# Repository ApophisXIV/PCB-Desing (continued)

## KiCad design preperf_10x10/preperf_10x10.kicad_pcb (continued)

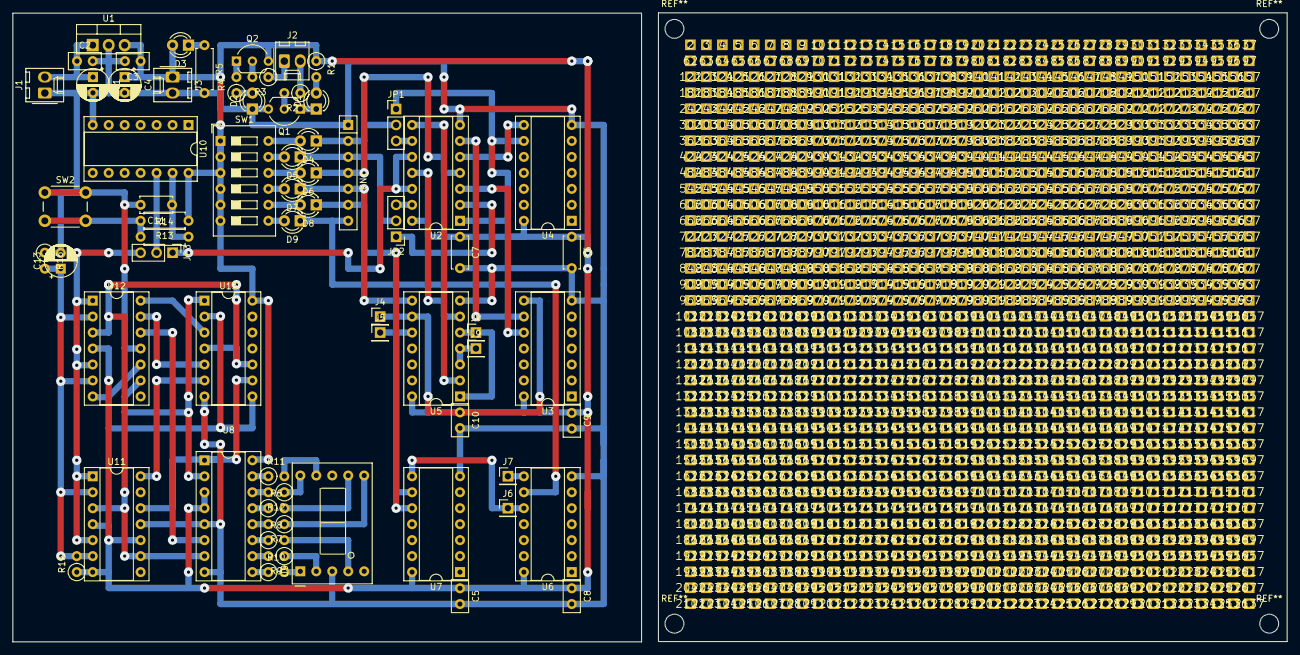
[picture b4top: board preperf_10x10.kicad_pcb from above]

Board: 2 copper layers, 202.7 x 100.1 mm, 1363 parts (0 on the bottom side), 67 nets.

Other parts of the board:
2, 3, 4, 5, 6, 7, 8, 9, 10, 11, 12, 13, 14, 15, 16, 17, 18, 19, 20, 21, 22, 23, 24, 25, 26, 27, 28, 29, 30, 31, 32, 33, 34, 35, 36, 37, 62, 63, 64, 65, 66, 67, 68, 69, 70, 71, 72, 73, 74, 75, 76, 77, 78, 79, 80, 81, 82, 83, 84, 85, 86, 87, 88, 89, 90, 91, 92, 93, 94, 95, 96, 97, 122, 123, 124, 125, 126, 127, 128, 129, 130, 131, 132, 133, 134, 135, 136, 137, 138, 139, 140, 141, 142, 143, 144, 145, 146, 147, 148, 149, 150, 151, 152, 153, 154, 155, 156, 157, 182, 183, 184, 185, 186, 187, 188, 189, 190, 191, 192, 193, 194, 195, 196, 197, 198, 199, 200, 201, 202, 203, 204, 205, 206, 207, 208, 209, 210, 211, 212, 213, 214, 215, 216, 217, 242, 243, 244, 245, 246, 247, 248, 249, 250, 251, 252, 253, 254, 255, 256, 257, 258, 259, 260, 261, 262, 263, 264, 265, 266, 267, 268, 269, 270, 271, 272, 273, 274, 275, 276, 277, 302, 303, 304, 305, 306, 307, 308, 309, 310, 311, 312, 313, 314, 315, 316, 317, 318, 319, 320, 321, 322, 323, 324, 325, 326, 327, 328, 329, 330, 331, 332, 333, 334, 335, 336, 337, 362, 363, 364, 365, 366, 367, 368, 369, 370, 371, 372, 373, 374, 375, 376, 377, 378, 379, 380, 381, 382, 383, 384, 385, 386, 387, 388, 389, 390, 391, 392, 393, 394, 395, 396, 397, 422, 423, 424, 425, 426, 427, 428, 429, 430, 431, 432, 433, 434, 435, 436, 437, 438, 439, 440, 441, 442, 443, 444, 445, 446, 447, 448, 449, 450, 451, 452, 453, 454, 455, 456, 457, 482, 483, 484, 485, 486, 487, 488, 489, 490, 491, 492, 493, 494, 495, 496, 497, 498, 499, 500, 501, 502, 503, 504, 505, 506, 507, 508, 509, 510, 511, 512, 513, 514, 515, 516, 517, 542, 543, 544, 545, 546, 547, 548, 549, 550, 551, 552, 553, 554, 555, 556, 557, 558, 559, 560, 561, 562, 563, 564, 565, 566, 567, 568, 569, 570, 571, 572, 573, 574, 575, 576, 577, 602, 603, 604, 605, 606, 607, 608, 609, 610, 611, 612, 613, 614, 615, 616, 617, 618, 619, 620, 621, 622, 623, 624, 625, 626, 627, 628, 629, 630, 631, 632, 633, 634, 635, 636, 637, 662, 663, 664, 665, 666, 667, 668, 669, 670, 671, 672, 673, 674, 675, 676, 677, 678, 679, 680, 681, 682, 683, 684, 685, 686, 687, 688, 689, 690, 691, 692, 693, 694, 695, 696, 697, 722, 723, 724, 725, 726, 727, 728, 729, 730, 731, 732, 733, 734, 735, 736, 737, 738, 739, 740, 741, 742, 743, 744, 745, 746, 747, 748, 749, 750, 751, 752, 753, 754, 755, 756, 757, 782, 783, 784, 785, 786, 787, 788, 789, 790, 791, 792, 793, 794, 795, 796, 797, 798, 799, 800, 801, 802, 803, 804, 805, 806, 807, 808, 809, 810, 811, 812, 813, 814, 815, 816, 817, 842, 843, 844, 845, 846, 847, 848, 849, 850, 851, 852, 853, 854, 855, 856, 857, 858, 859, 860, 861, 862, 863, 864, 865, 866, 867, 868, 869, 870, 871, 872, 873, 874, 875, 876, 877, 902, 903, 904, 905, 906, 907, 908, 909, 910, 911, 912, 913, 914, 915, 916, 917, 918, 919, 920, 921, 922, 923, 924, 925, 926, 927, 928, 929, 930, 931, 932, 933, 934, 935, 936, 937, 962, 963, 964, 965, 966, 967, 968, 969, 970, 971, 972, 973, 974, 975, 976, 977, 978, 979, 980, 981, 982, 983, 984, 985, 986, 987, 988, 989, 990, 991, 992, 993, 994, 995, 996, 997, 1022, 1023, 1024, 1025, 1026, 1027, 1028, 1029, 1030, 1031, 1032, 1033, 1034, 1035, 1036, 1037, 1038, 1039, 1040, 1041, 1042, 1043, 1044, 1045, 1046, 1047, 1048, 1049, 1050, 1051, 1052, 1053, 1054, 1055, 1056, 1057, 1082, 1083, 1084, 1085, 1086, 1087, 1088, 1089, 1090, 1091, 1092, 1093, 1094, 1095, 1096, 1097, 1098, 1099, 1100, 1101, 1102, 1103, 1104, 1105, 1106, 1107, 1108, 1109, 1110, 1111, 1112, 1113, 1114, 1115, 1116, 1117, 1142, 1143, 1144, 1145, 1146, 1147, 1148, 1149, 1150, 1151, 1152, 1153, 1154, 1155, 1156, 1157, 1158, 1159, 1160, 1161, 1162, 1163, 1164, 1165, 1166, 1167, 1168, 1169, 1170, 1171, 1172, 1173, 1174, 1175, 1176, 1177, 1202, 1203, 1204, 1205, 1206, 1207, 1208, 1209, 1210, 1211, 1212, 1213, 1214, 1215, 1216, 1217, 1218, 1219, 1220, 1221, 1222, 1223, 1224, 1225, 1226, 1227, 1228, 1229, 1230, 1231, 1232, 1233, 1234, 1235, 1236, 1237, 1262, 1263, 1264, 1265, 1266, 1267, 1268, 1269, 1270, 1271, 1272, 1273, 1274, 1275, 1276, 1277, 1278, 1279, 1280, 1281, 1282, 1283, 1284, 1285, 1286, 1287, 1288, 1289, 1290, 1291, 1292, 1293, 1294, 1295, 1296, 1297, 1322, 1323, 1324, 1325, 1326, 1327, 1328, 1329, 1330, 1331, 1332, 1333, 1334, 1335, 1336, 1337, 1338, 1339, 1340, 1341, 1342, 1343, 1344, 1345, 1346, 1347, 1348, 1349, 1350, 1351, 1352, 1353, 1354, 1355, 1356, 1357, 1382, 1383, 1384, 1385, 1386, 1387, 1388, 1389, 1390, 1391, 1392, 1393, 1394, 1395, 1396, 1397, 1398, 1399, 1400, 1401, 1402, 1403, 1404, 1405, 1406, 1407, 1408, 1409, 1410, 1411, 1412, 1413, 1414, 1415, 1416, 1417, 1442, 1443, 1444, 1445, 1446, 1447, 1448, 1449, 1450, 1451, 1452, 1453, 1454, 1455, 1456, 1457, 1458, 1459, 1460, 1461, 1462, 1463, 1464, 1465, 1466, 1467, 1468, 1469, 1470, 1471, 1472, 1473, 1474, 1475, 1476, 1477, 1502, 1503, 1504, 1505, 1506, 1507, 1508, 1509, 1510, 1511, 1512, 1513, 1514, 1515, 1516, 1517, 1518, 1519, 1520, 1521, 1522, 1523, 1524, 1525, 1526, 1527, 1528, 1529, 1530, 1531, 1532, 1533, 1534, 1535, 1536, 1537, 1562, 1563, 1564, 1565, 1566, 1567, 1568, 1569, 1570, 1571, 1572, 1573, 1574, 1575, 1576, 1577, 1578, 1579, 1580, 1581, 1582, 1583, 1584, 1585, 1586, 1587, 1588, 1589, 1590, 1591, 1592, 1593, 1594, 1595, 1596, 1597, 1622, 1623, 1624, 1625, 1626, 1627, 1628, 1629, 1630, 1631, 1632, 1633, 1634, 1635, 1636, 1637, 1638, 1639, 1640, 1641, 1642, 1643, 1644, 1645, 1646, 1647, 1648, 1649, 1650, 1651, 1652, 1653, 1654, 1655, 1656, 1657, 1682, 1683, 1684, 1685, 1686, 1687, 1688, 1689, 1690, 1691, 1692, 1693, 1694, 1695, 1696, 1697, 1698, 1699, 1700, 1701, 1702, 1703, 1704, 1705, 1706, 1707, 1708, 1709, 1710, 1711, 1712, 1713, 1714, 1715, 1716, 1717, 1742, 1743, 1744, 1745, 1746, 1747, 1748, 1749, 1750, 1751, 1752, 1753, 1754, 1755, 1756, 1757, 1758, 1759, 1760, 1761, 1762, 1763, 1764, 1765, 1766, 1767, 1768, 1769, 1770, 1771, 1772, 1773, 1774, 1775, 1776, 1777, 1802, 1803, 1804, 1805, 1806, 1807, 1808, 1809, 1810, 1811, 1812, 1813, 1814, 1815, 1816, 1817, 1818, 1819, 1820, 1821, 1822, 1823, 1824, 1825, 1826, 1827, 1828, 1829, 1830, 1831, 1832, 1833, 1834, 1835, 1836, 1837, 1862, 1863, 1864, 1865, 1866, 1867, 1868, 1869, 1870, 1871, 1872, 1873, 1874, 1875, 1876, 1877, 1878, 1879, 1880, 1881, 1882, 1883, 1884, 1885, 1886, 1887, 1888, 1889, 1890, 1891, 1892, 1893, 1894, 1895, 1896, 1897, 1922, 1923, 1924, 1925, 1926, 1927, 1928, 1929, 1930, 1931, 1932, 1933, 1934, 1935, 1936, 1937, 1938, 1939, 1940, 1941, 1942, 1943, 1944, 1945, 1946, 1947, 1948, 1949, 1950, 1951, 1952, 1953, 1954, 1955, 1956, 1957, 1982, 1983, 1984, 1985, 1986, 1987, 1988, 1989, 1990, 1991, 1992, 1993, 1994, 1995, 1996, 1997, 1998, 1999, 2000, 2001, 2002, 2003, 2004, 2005, 2006, 2007, 2008, 2009, 2010, 2011, 2012, 2013, 2014, 2015, 2016, 2017, 2042, 2043, 2044, 2045, 2046, 2047, 2048, 2049, 2050, 2051, 2052, 2053, 2054, 2055, 2056, 2057, 2058, 2059, 2060, 2061, 2062, 2063, 2064, 2065, 2066, 2067, 2068, 2069, 2070, 2071, 2072, 2073, 2074, 2075, 2076, 2077, 2102, 2103, 2104, 2105, 2106, 2107, 2108, 2109, 2110, 2111, 2112, 2113, 2114, 2115, 2116, 2117, 2118, 2119, 2120, 2121, 2122, 2123, 2124, 2125, 2126, 2127, 2128, 2129, 2130, 2131, 2132, 2133, 2134, 2135, 2136, 2137: (no value)

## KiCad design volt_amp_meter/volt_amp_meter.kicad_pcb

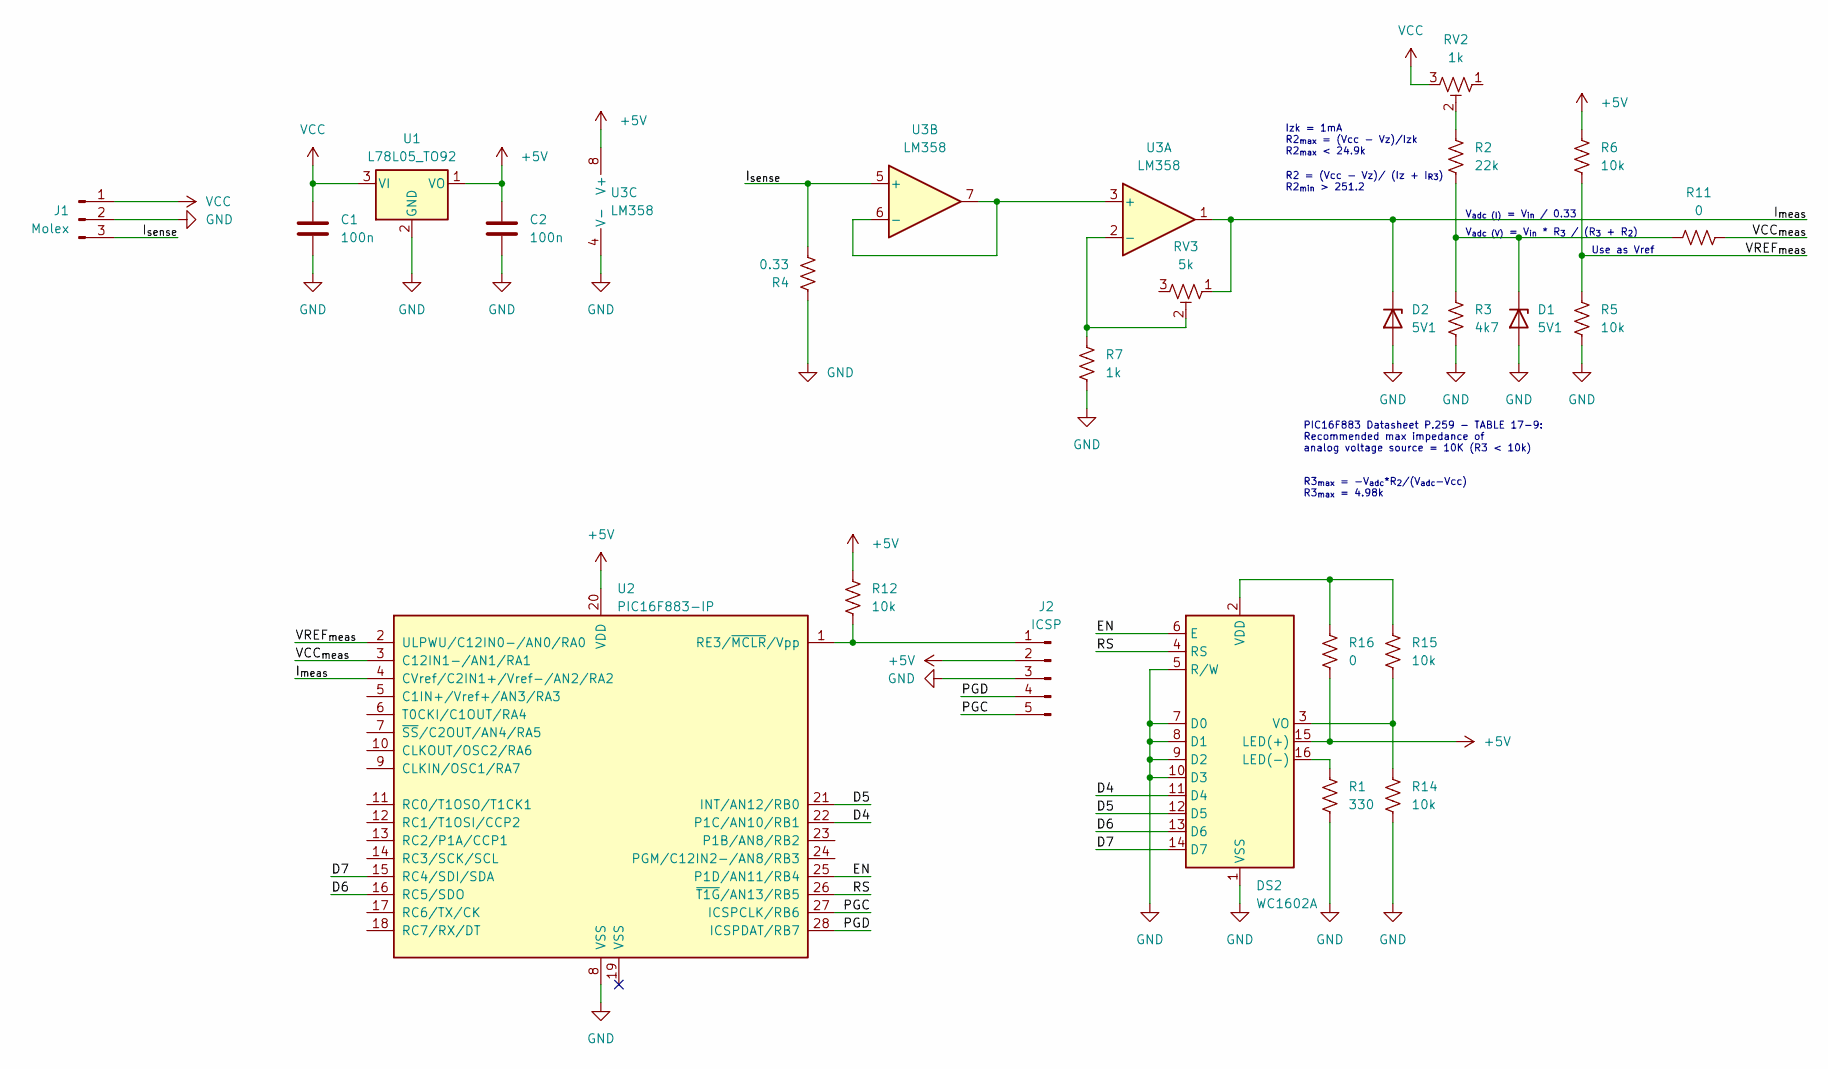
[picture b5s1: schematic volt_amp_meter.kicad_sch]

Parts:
C1, C2: 100n; C_1206_3216Metric_Pad1.33x1.80mm_HandSolder
D1, D2: 5V1; D_MiniMELF
DS2: WC1602A
J1: Molex; Molex_SPOX_5268-03A_1x03_P2.50mm_Horizontal
J2: ICSP; PinHeader_1x05_P2.54mm_Horizontal
R1: 330; R_0805_2012Metric_Pad1.20x1.40mm_HandSolder
R2: 22k; R_1206_3216Metric_Pad1.30x1.75mm_HandSolder
R3: 4k7; R_1206_3216Metric_Pad1.30x1.75mm_HandSolder
R4: 0.33; R_Axial_Power_L20.0mm_W6.4mm_P25.40mm
R5, R6, R12, R14, R15: 10k; R_1206_3216Metric_Pad1.30x1.75mm_HandSolder
R7: 1k; R_0805_2012Metric_Pad1.20x1.40mm_HandSolder
R11, R16: 0; R_1206_3216Metric_Pad1.30x1.75mm_HandSolder
RV2: 1k; Potentiometer_Bourns_3386C_Horizontal
RV3: 5k; Potentiometer_Bourns_3386C_Horizontal
U1: L78L05_TO92; TO-92_Inline
U2: PIC16F883-IP; DIP-28_W7.62mm_Socket_LongPads
U3: LM358; SOIC-8_3.9x4.9mm_P1.27mm

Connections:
+5V: C2.1, DS2.15 (LED(+)), J2.2, R6.2, R12.2, R16.1, U1.1 (VO), U2.20 (VDD), U3.8 (V+)
/D4: DS2.11 (D4), U2.22 (P1C/AN10/RB1)
/D5: DS2.12 (D5), U2.21 (INT/AN12/RB0)
/D6: DS2.13 (D6), U2.16 (RC5/SDO)
/D7: DS2.14 (D7), U2.15 (RC4/SDI/SDA)
/EN: DS2.6 (E), U2.25 (P1D/AN11/RB4)
/I_{meas}: D2.1 (K), RV3.1, U2.4 (CVref/C2IN1+/Vref-/AN2/RA2), U3.1
/I_{sense}: J1.3, R4.1, U3.5 (+)
/PGC: J2.5, U2.27 (ICSPCLK/RB6)
/PGD: J2.4, U2.28 (ICSPDAT/RB7)
/RS: DS2.4 (RS), U2.26 (~T1G/AN13/RB5)
/VCC_{meas}: R11.1, U2.3 (C12IN1-/AN1/RA1)
/VREF_{meas}: R5.2, R6.1, U2.2 (ULPWU/C12IN0-/AN0/RA0)
GND: C1.2, C2.2, D1.2 (A), D2.2 (A), DS2.1 (VSS), DS2.5 (R/W), DS2.7 (D0), DS2.8 (D1), DS2.9 (D2), DS2.10 (D3), J1.2, J2.3, R1.1, R3.1, R4.2, R5.1, R7.2, R14.1, U1.2 (GND), U2.8 (VSS), U3.4 (V-)
unnamed: D1.1 (K), R2.1, R3.2, R11.2
unnamed: DS2.16 (LED(-)), R1.2
unnamed: DS2.2 (VDD), R15.2, R16.2
unnamed: DS2.3 (VO), R14.2, R15.1
unnamed: J2.1, R12.1, U2.1 (RE3/~MCLR/Vpp)
unnamed: R2.2, RV2.2
unnamed: U3.3 (+), U3.6 (-), U3.7
unnamed: R7.1, RV3.2, U3.2 (-)
VCC: C1.1, J1.1, RV2.3, U1.3 (VI)

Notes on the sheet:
Izk = 1mA R2_{max} = (Vcc - Vz)/Izk R2_{max} < 24.9k
V_{adc (I)} = V_{in} / 0.33
Use as Vref
R2 = (Vcc - Vz)/ (Iz + I_{R3}) R2_{min} > 251.2
PIC16F883 Datasheet P.259 - TABLE 17-9: Recommended max impedance of analog voltage source = 10K (R3 < 10k)
R3_{max} = -V_{adc}*R_{2}/(V_{adc}-Vcc) R3_{max} = 4.98k
V_{adc (V)} = V_{in} * R_{3} / (R_{3} + R_{2})

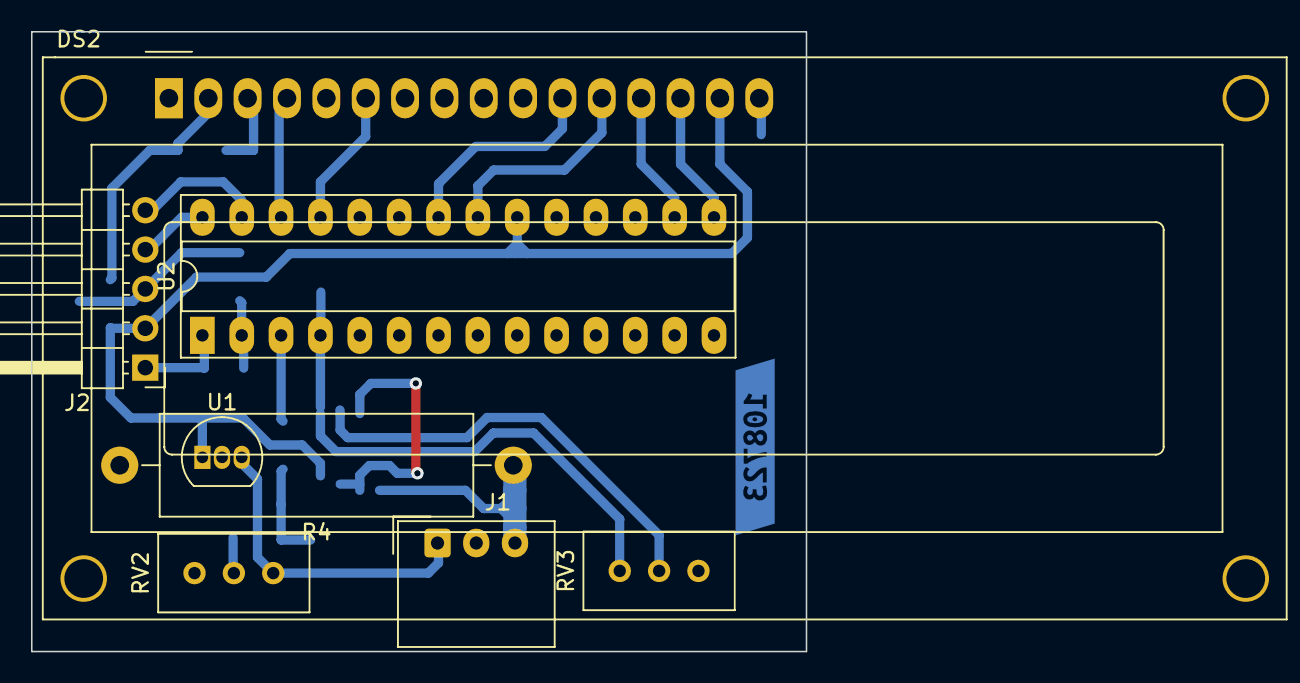
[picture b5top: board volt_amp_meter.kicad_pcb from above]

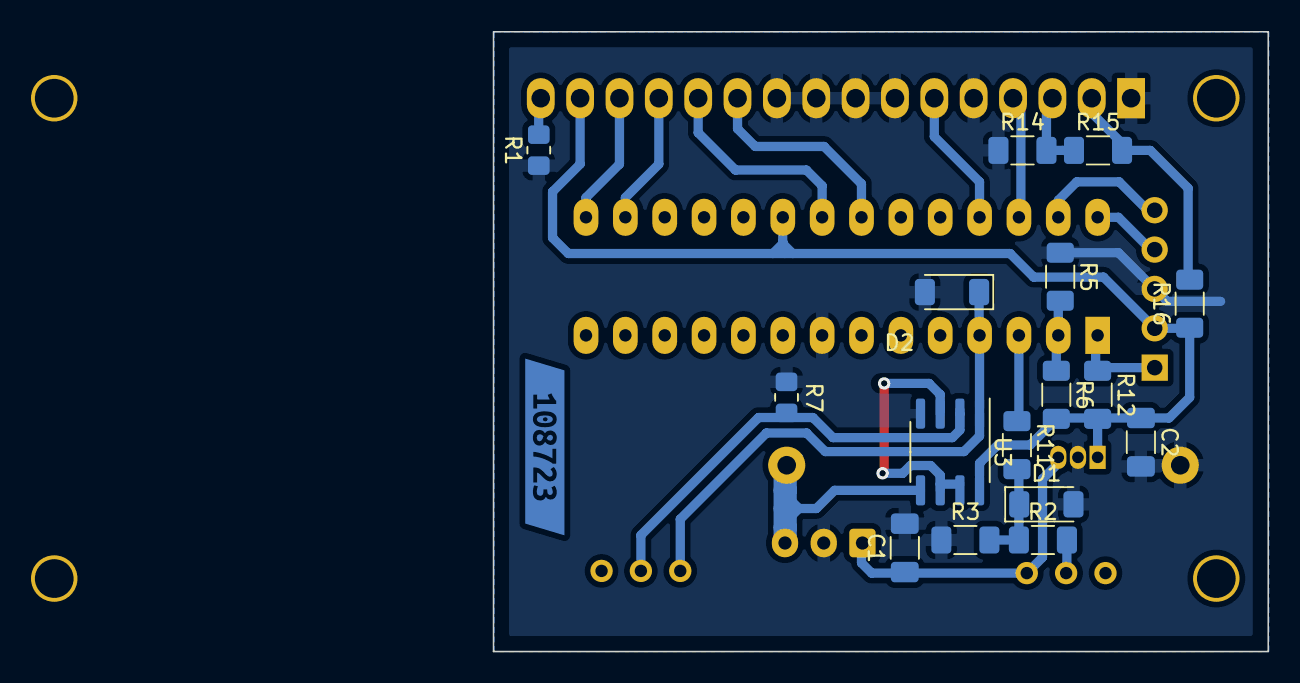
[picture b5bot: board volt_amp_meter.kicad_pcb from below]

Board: 2 copper layers, 50.0 x 40.0 mm, 25 parts (17 on the bottom side), 23 nets.

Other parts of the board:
kibuzzard-6583EB80: G***; kibuzzard-6583EB80

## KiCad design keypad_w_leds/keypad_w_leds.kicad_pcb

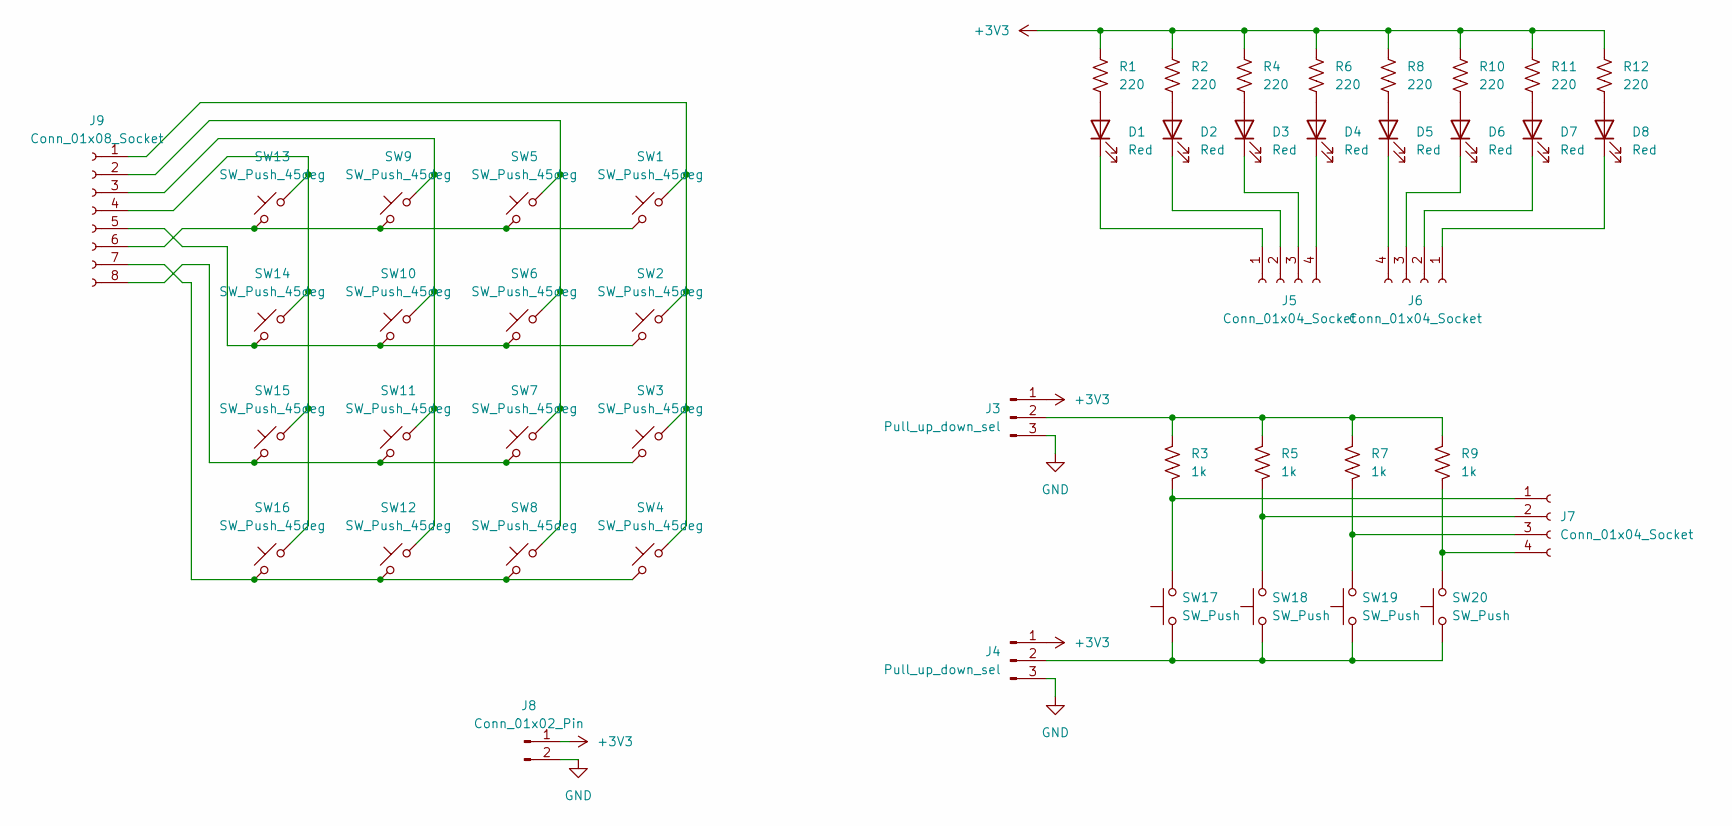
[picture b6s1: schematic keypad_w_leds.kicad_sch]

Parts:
D1, D2, D3, D4, D5, D6, D7, D8: Red; LED_0805_2012Metric_Pad1.15x1.40mm_HandSolder
J3, J4: Pull_up_down_sel; PinHeader_1x03_P2.54mm_Vertical
J5, J6, J7: Conn_01x04_Socket; PinSocket_1x04_P2.54mm_Vertical
J8: Conn_01x02_Pin; PinHeader_1x02_P2.54mm_Vertical
J9: Conn_01x08_Socket; PinSocket_1x08_P2.54mm_Vertical
R1, R2, R4, R6, R8, R10, R11, R12: 220; R_0805_2012Metric_Pad1.20x1.40mm_HandSolder
R3, R5, R7, R9: 1k; R_0805_2012Metric_Pad1.20x1.40mm_HandSolder
SW1, SW2, SW3, SW4, SW5, SW6, SW7, SW8, SW9, SW10, SW11, SW12, SW13, SW14, SW15, SW16: SW_Push_45deg; SW_PUSH_6mm_H5mm
SW17, SW18, SW19, SW20: SW_Push; SW_PUSH_6mm_H5mm

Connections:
+3V3: J3.1, J4.1, J8.1, R1.1, R2.1, R4.1, R6.1, R8.1, R10.1, R11.1, R12.1
GND: J3.3, J4.3, J8.2
unnamed: D1.2 (A), R1.2
unnamed: D1.1 (K), J5.1
unnamed: D2.2 (A), R2.2
unnamed: D2.1 (K), J5.2
unnamed: D3.2 (A), R4.2
unnamed: D3.1 (K), J5.3
unnamed: D4.2 (A), R6.2
unnamed: D4.1 (K), J5.4
unnamed: D5.2 (A), R8.2
unnamed: D5.1 (K), J6.4
unnamed: D6.2 (A), R10.2
unnamed: D6.1 (K), J6.3
unnamed: D7.2 (A), R11.2
unnamed: D7.1 (K), J6.2
unnamed: D8.2 (A), R12.2
unnamed: D8.1 (K), J6.1
unnamed: J3.2, R3.1, R5.1, R7.1, R9.1
unnamed: J4.2, SW17.2, SW18.2, SW19.2, SW20.2
unnamed: J7.1, R3.2, SW17.1
unnamed: J7.2, R5.2, SW18.1
unnamed: J7.3, R7.2, SW19.1
unnamed: J7.4, R9.2, SW20.1
unnamed: J9.1, SW1.1, SW2.1, SW3.1, SW4.1
unnamed: J9.2, SW5.1, SW6.1, SW7.1, SW8.1
unnamed: J9.3, SW9.1, SW10.1, SW11.1, SW12.1
unnamed: J9.4, SW13.1, SW14.1, SW15.1, SW16.1
unnamed: J9.5, SW2.2, SW6.2, SW10.2, SW14.2
unnamed: J9.6, SW1.2, SW5.2, SW9.2, SW13.2
unnamed: J9.7, SW4.2, SW8.2, SW12.2, SW16.2
unnamed: J9.8, SW3.2, SW7.2, SW11.2, SW15.2

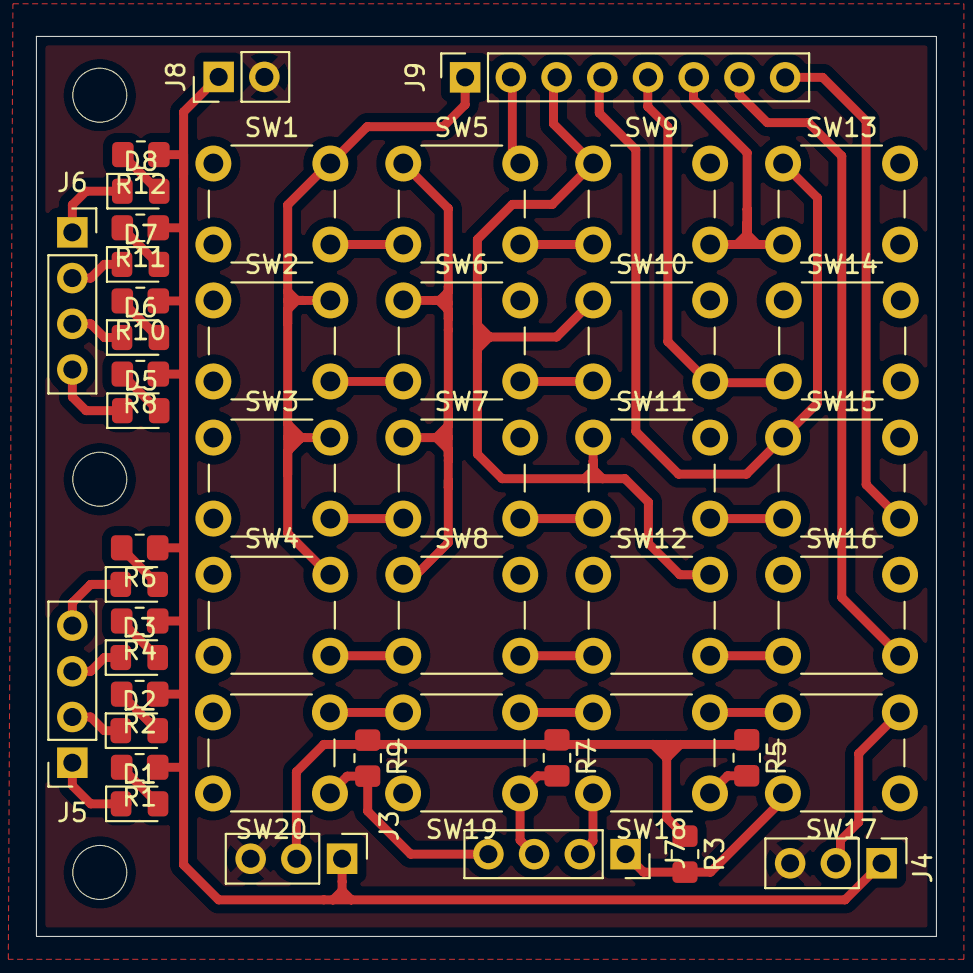
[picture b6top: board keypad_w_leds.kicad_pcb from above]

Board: 2 copper layers, 50.0 x 50.0 mm, 47 parts (0 on the bottom side), 32 nets.

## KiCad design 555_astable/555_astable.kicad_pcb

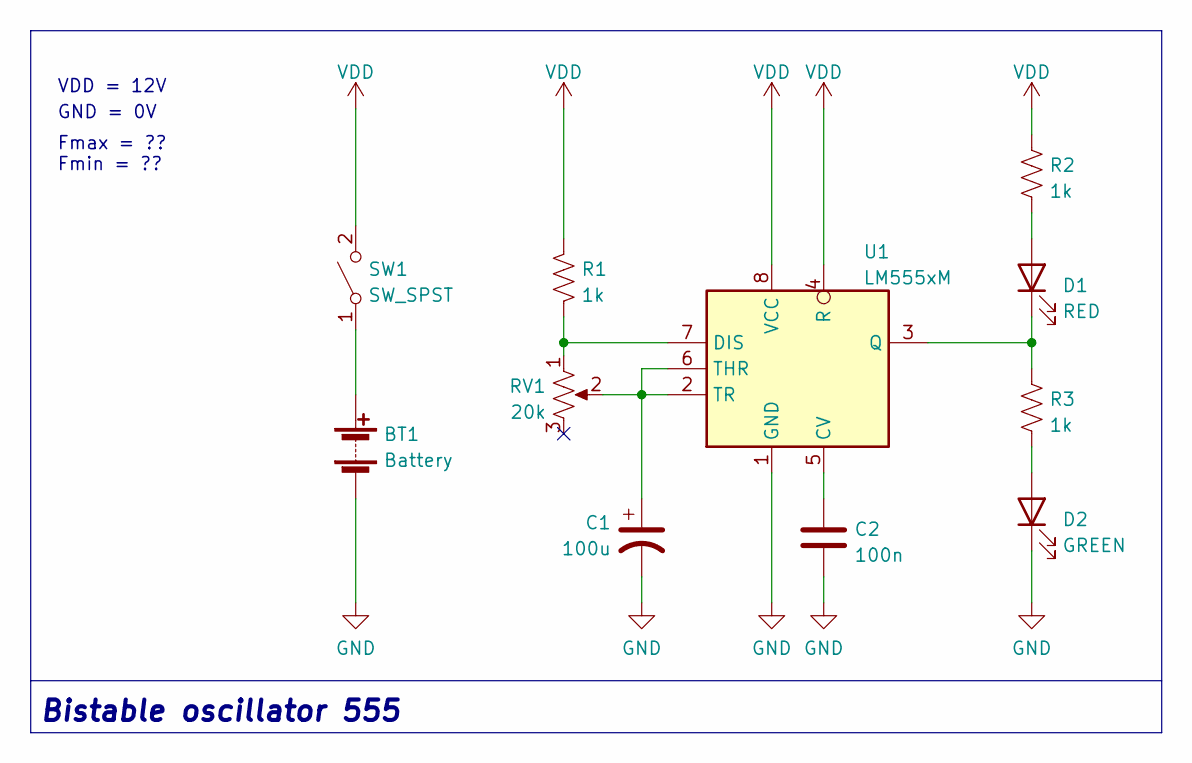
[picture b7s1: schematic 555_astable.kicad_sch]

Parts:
BT1: Battery; PinSocket_1x02_P2.54mm_Vertical
C1: 100u; CP_Elec_6.3x5.4
C2: 100n; C_0805_2012Metric_Pad1.18x1.45mm_HandSolder
D1: RED; LED_0805_2012Metric_Pad1.15x1.40mm_HandSolder
D2: GREEN; LED_0805_2012Metric_Pad1.15x1.40mm_HandSolder
R1, R2, R3: 1k; R_0805_2012Metric_Pad1.20x1.40mm_HandSolder
RV1: 20k; PinSocket_1x02_P2.54mm_Vertical
SW1: SW_SPST; PinSocket_1x02_P2.54mm_Vertical
U1: LM555xM; SOIC-8_3.9x4.9mm_P1.27mm

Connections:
GND: BT1.2 (-), C1.2, C2.2, D2.1 (K), U1.1 (GND)
unnamed: BT1.1 (+), SW1.1 (A)
unnamed: C1.1, RV1.2, U1.2 (TR), U1.6 (THR)
unnamed: C2.1, U1.5 (CV)
unnamed: D1.1 (K), R3.1, U1.3 (Q)
unnamed: D1.2 (A), R2.2
unnamed: D2.2 (A), R3.2
unnamed: R1.2, RV1.1, U1.7 (DIS)
VDD: R1.1, R2.1, SW1.2 (B), U1.4 (R), U1.8 (VCC)

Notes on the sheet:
Bistable oscillator 555
VDD = 12V
GND = 0V
Fmax = ?? Fmin = ??

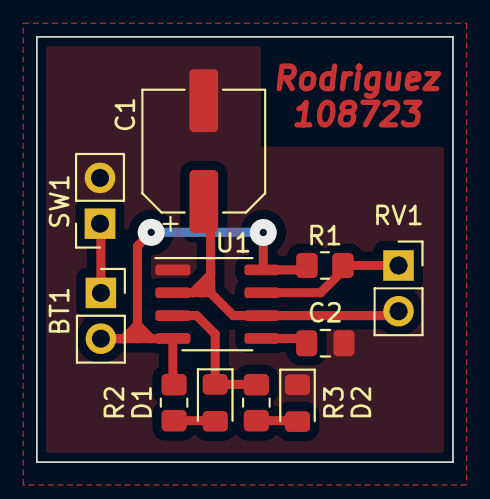
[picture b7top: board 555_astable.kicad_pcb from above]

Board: 2 copper layers, 23.1 x 23.6 mm, 11 parts (0 on the bottom side), 9 nets.

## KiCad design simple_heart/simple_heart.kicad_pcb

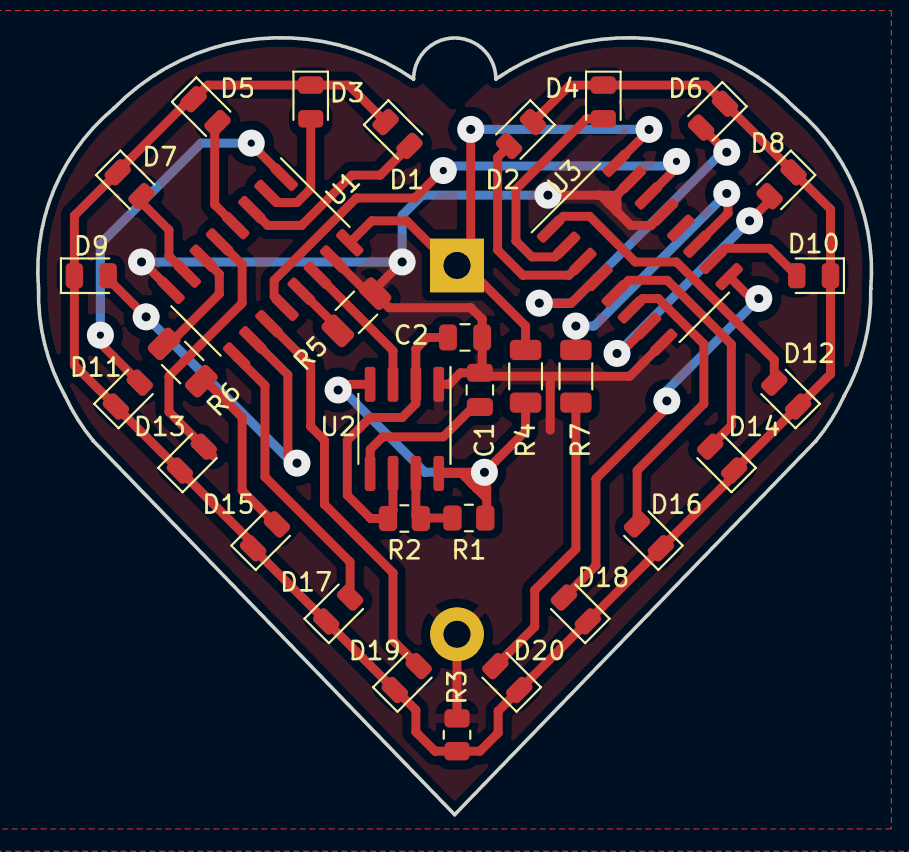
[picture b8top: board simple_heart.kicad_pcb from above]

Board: 2 copper layers, 46.3 x 43.2 mm, 33 parts (1 on the bottom side), 32 nets.

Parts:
BT1: CR2032; BatteryHolder_Keystone_103_1x20mm
C1: 10nF; C_0805_2012Metric
C2: 100nF; C_0805_2012Metric
D1, D2, D3, D4, D5, D6, D7, D8, D9, D10, D11, D12, D13, D14, D15, D16, D17, D18, D19, D20: Red; LED_0805_2012Metric
R1: 4.7k; R_0805_2012Metric
R2: 470k; R_0805_2012Metric
R3: 330; R_0805_2012Metric
R4, R5, R6, R7: 0; R_1206_3216Metric
U1, U3: 4017; SO-16_3.9x9.9mm_P1.27mm
U2: LM555xM; SOIC-8_3.9x4.9mm_P1.27mm

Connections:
+BATT: BT1.1 (+), R4.2, U1.16 (VDD), U3.16 (VDD)
/CLK: U1.14 (CLK), U2.3 (Q)
/F/10: U1.12 (Cout), U3.14 (CLK)
/LED1: D1.2 (A), U1.3 (Q0)
/LED2: D3.2 (A), U1.2 (Q1)
/LED3: D5.2 (A), U1.4 (Q2)
/LED4: D7.2 (A), U1.7 (Q3)
/LED5: D9.2 (A), U1.10 (Q4)
/LED6: D11.2 (A), U1.1 (Q5)
/LED7: D13.2 (A), U1.5 (Q6)
/LED8: R6.2, U1.6 (Q7)
/LED9: D17.2 (A), U1.9 (Q8)
/LED10: D19.2 (A), U1.11 (Q9)
/LED11: D2.2 (A), U3.3 (Q0)
/LED12: D4.2 (A), U3.2 (Q1)
/LED13: D6.2 (A), U3.4 (Q2)
/LED14: D8.2 (A), U3.7 (Q3)
/LED15: D10.2 (A), U3.10 (Q4)
/LED16: D12.2 (A), U3.1 (Q5)
/LED17: D14.2 (A), U3.5 (Q6)
/LED18: D16.2 (A), U3.6 (Q7)
/LED19: D18.2 (A), U3.9 (Q8)
/LED20: R7.2, U3.11 (Q9)
GND: BT1.2 (-), C1.2, C2.2, R3.1, R5.1, U1.8 (VSS), U1.15 (Reset), U2.1 (GND), U3.8 (VSS), U3.13 (CKEN), U3.15 (Reset)
unnamed: C1.1, U2.5 (CV)
unnamed: C2.1, R2.1, U2.2 (TR), U2.6 (THR)
unnamed: D1.1 (K), D2.1 (K), D3.1 (K), D4.1 (K), D5.1 (K), D6.1 (K), D7.1 (K), D8.1 (K), D9.1 (K), D10.1 (K), D11.1 (K), D12.1 (K), D13.1 (K), D14.1 (K), D15.1 (K), D16.1 (K), D17.1 (K), D18.1 (K), D19.1 (K), D20.1 (K), R3.2
unnamed: D15.2 (A), R6.1
unnamed: D20.2 (A), R7.1
unnamed: R1.1, R2.2, U2.7 (DIS)
unnamed: R1.2, R4.1, U2.4 (R), U2.8 (VCC)
unnamed: R5.2, U1.13 (CKEN)

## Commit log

2022-09-22 First commit. WIP
2022-09-25 Circuit almost finished
2022-09-25 PCB Finished
2022-09-25 Add PCB pdf ready to print
2022-09-27 Update schematic
2022-11-01 Update gitignore
2022-11-01 Delete
2022-11-01 Electrect microphone amplifier
2023-06-26 Pseudo walkie talkie - design for IIE FIUBA 1C2023
2023-06-26 555 astable
2023-06-26 Create fp-info-cache
2023-06-26 Mic preamp
2023-08-29 PSU LM317 with protections
2023-08-29 Lab project IIE-1C2023
2023-08-29 Lab project TD-2C2023
2023-09-12 Added TP2, TP3 and TP4
2023-09-24 "TP2" and "TP3" digital techniques
2023-09-29 Update. Delete TP4
2023-10-20 Added BCD Up counter with JK FF
2023-11-24 Added BCD Counter UP (FF JK based) and Power-On-Reset
2023-11-25 Fix BCD UP counter
2024-01-08 Cleaned up
2024-01-08 PSU Volt-Amp meter PIC Mcu based
2024-01-08 Simple PSU LM317 based
2025-01-13 Monopoly with electronic bank [WIP] - Keypad w/sound
2025-04-17 [ADD] 4x4 Keypad with selectable 4 pull-up/down buttons
2025-04-17 [ADD] PCB render
2025-04-17 [ADD] 3D models
2025-04-17 [ADD] IR remote control based on HT12E/D ICs (I Recommend HT12A/F)
    Toy project for local manufacture test
2025-04-17 [ADD] .lck files to gitignore
2025-04-17 [ADD] Panel volt-amp meter from 0-30V and 0-3A (minimal protections)
2025-04-17 [ADD] Useful lib with 3D models for common use modules
2025-04-17 [UPDATE] Add PCB render
2025-04-17 [ADD] Digital Logic Design project (FIUBA): PCB implementation of schmitt triggers, logic functions, counters, state machines, and logic probes
2025-04-17 [ADD] gitignore
2025-04-18 [ADD] LPC845-based development board for oximeter with integrated WiFi module
    Custom development board commissioned for a client project. Features:
    - LPC845 microcontroller
    - MAX30102 pulse oximeter sensor
    - WiFi module for real-time data communication
    - Custom PCB layout and hardware integration
    Includes all design files, schematics and pcb
2025-04-18 [ADD] Some test related with .cir, . and simulation models for ASK/OOK RF module
    * ASK / OOK transmitter
    * 433.92 MHz 10mW 5V
    .model RF_Switch SW(Ron=0.01 Roff=1g Vt=2.5 Vh=0)
    .subckt FS1000A VCC Data GND
    * /
    * /
2025-04-18 [ADD] Banana, Bornier, LCD1602 and LPC845 3D models
2025-04-18 [ADD] Toy project - 555 astable in SMD and THT
2025-04-18 [ADD] 3D models and PCB substrate colors definitions
2025-04-18 [ADD] LM317 CV PSU (with minimal protecctions)
    WIP - Add CC protections
